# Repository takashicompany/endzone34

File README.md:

# EndZone34

ミニマルな34キーのキーボードです。  
LEDとOLED、MXソケットに対応しています。

# 組み立て方

## ビルドログ

- [いとうひよこさんのNote](https://note.com/tsubuan_145/n/n91b1f3b4b958)

## 1. 部品の確認

### キットに同梱されているもの

|項目|個数|備考|
|:--|:--|:--|
|PCB|1|
|トッププレート|1|
|ボトムプレート|1|
|側面プレート|2|左右有り。キースイッチをMXソケットで取り付ける場合は不要|
|ProMicroプレート|1|
|ProMicro側面プレート|2|
|M2ネジ 10mm|18|
|M2ナット|18|
|ダイオード|34|
|リセットスイッチ|1|
|ゴム足シール|8|

### ご自身で用意されるもの
|項目|個数|備考|
|:--|:--|:--|
|キースイッチ|34|Cherry MX互換|
|キーキャップ|34|
|Pro Micro|1|必要な場合はコンスルーもご用意ください|

### MXソケットを利用する際に必要な部品

PCBがMXソケットに対応しているため、スペーサーとネジを別途ご用意頂き、キースイッチの付け替えが可能になります。
(MXソケットを使用する場合は側面プレートを取り付けることはできません。)

|項目|個数|備考|
|:--|:--|:--|
|MXソケット|34||
|両雌ネジスペーサー 7mm|8|
|M2ネジ 4mm|16|

## 2. ダイオードのはんだ付け

### ① PCBの裏表の確認

**こちらが表面**  

**こちらは裏面**  

はんだ付けは**裏面**に行います

### ① マスキングテープで表面にはんだが漏れないようにする

(テープを見えやすくするために黒色のPCBで説明します)  

当キットではトッププレートとPCBを密着させる方式なので、表面にはんだが漏れて凹凸ができないように、マスキングテープなどで穴を塞ぎましょう。

### ② ダイオードをはんだづけする

https://user-images.githubusercontent.com/4215759/126895350-43ae4cd4-408b-4ff4-ab5c-2903e0420978.mov

PCBのダイオードのはんだづけ箇所の片方にはんだを乗せておき(予備はんだ)、ピンセットでダイオードを持ちながら予備はんだを溶かしながらダイオードをはんだづけします。  
片方のはんだづけが終わったら、動画と同じく反対側をはんだづけしましょう。

全部で34箇所あります。

## 3-a. キースイッチのはんだ付け

キースイッチをはんだ付けする場合は、以下の手順になります。

### ① トッププレートを取り出す

アクリル製のトッププレートを取り出します。  

ネジ穴部分にアクリル栓が詰まっている場合は、ピンセットやネジで押し出すと取り出すことができます。  
全てのネジ穴が空いていることを確認しましょう。  

トッププレートの台紙を剥がします。   
剥がしづらい場合は、台紙を少し濡らすと剥がれやすくなります。

下記の画像のように両面を剥がします。  

### ② トッププレートを仮止め

当キーボードキットは、PCBとトッププレートを密着させる必要があるため、キースイッチのはんだ付けの際にトッププレートがぐらつかないようにすると作業が楽になります。  
同梱しているネジとナットを使って、PCBの表側にトッププレートを固定しましょう。

あくまで仮止めですので、全ての箇所を固定しなくても問題ありません。
下記の画像は目安です。  
固定できたらPCBとトッププレートに隙間が無いことを確認してください。

### ③ キースイッチをはんだ付けする
PCBとトッププレートを固定できたら、キースイッチのはんだ付けを行います。  
キースイッチがズレないように、マスキングテープなどで固定すると作業が楽になります。

各キースイッチ、2箇所をはんだ付けします。  
**取付箇所毎にキースイッチの向きが異なります。**  

34個のキースイッチをはんだ付けできたら、高さがズレているものがないかを確認します。  
加えて、再びPCBとトッププレートの間に隙間が無いことを確認します。

## 3-b. MXソケットでキースイッチを取り付ける場合

キースイッチをMXソケットではんだ付けする際は、以下の方法になります。
なお、この場合は側面プレートではなく、スペーサーでトッププレートとボトムプレートを固定することとなります。

### ① PCBにMXソケットをはんだ付けする

### ② トッププレートを取り出す

「3-a. ① トッププレートを取り出す」と同様にトッププレートを取りだします。

### ③ トッププレートにキースイッチを取り付ける

PCBとトッププレートの仮止めとして、キースイッチを数個取り付けます。

以下は一例になります。  

キースイッチをいくつか取り付けた後に、PCBにはんだ付けしたMXソケットにトッププレートに仮止めしたキースイッチを取り付けます。

トッププレートがたわまないように気をつけながら、全てのMXソケットにキースイッチを付けていきます。

### ④ トッププレートにスペーサーを取り付ける

以下の赤丸の箇所にスペーサーを取り付けます。  
トッププレートとスペーサーをネジで固定します。  

下記の写真のように、トッププレートからネジで固定されたスペーサーがPCBを貫通してPCBの裏側に出ていると正しく取り付けられています。

## 4. リセットスイッチのはんだ付け
※リセットスイッチのはんだ付けは必須ではありません。組み立て後も、ピンセット等を用いて底面からリセット操作が可能です。

### ① PCBの裏面からリセットスイッチを差し込む

### ② PCBの表面からはんだづけをする

### ③ はんだ付けした部分を可能な限り平らにする

Pro Microとぶつかってしまう可能性があるので、ニッパーなどで平らにします。

### ④ 絶縁テープなどではんだ付け部分を覆う

## 5. Pro Microの取り付け

Pro Microをご用意いただきます。  
PCBはコンスルーとはんだ付けの両対応をしています。  

Pro Microのチップなどが載っていない方を表側にし、PCBの表側に指します。

一度ここで、ProMicroをPCなどに繋ぎ、ファームウェアを焼いて動作確認をすると問題があった際に、対処が容易です。  

ファームウェアは[こちら](https://github.com/takashicompany/endzone34/blob/master/README.md#%E3%83%95%E3%82%A1%E3%83%BC%E3%83%A0%E3%82%A6%E3%82%A7%E3%82%A2)。

## 6. Pro Microプレートの取り付け
まずはPro Microの側面プレートを取り付けます。  
側面プレートは二種類あるので、お好みで選んでください。  

台紙を剥がして、側面プレートを2枚トッププレートに載せます。    

次にPro Microプレートを取り付けます。  

台紙を剥がして、側面プレートの上に載せます。  

ネジとナットで固定します。  

裏面は下記の写真のようにナットで抑えます。  

MXソケットを利用する場合は、ナットの代わりにスペーサーを用いると良いです。

## 6. LEDの取り付け

LEDの取り付けは必須ではありません。一度組み立てた後で取り付けることでも可能です。  
LEDはWS2812Bを使用します。下記の画像の順番で取り付けます。 

取り付ける際に、PCBのプリント(角の塗りつぶし)とLEDの角の向きが合うようにします。 

まずは予備ハンダをします。利き腕側で手前の側の部分からはんだ付けをすると楽にできます。

一つのLEDの4箇所をはんだづけします。  

一つはんだ付けができたら、LEDが光るかを確認しましょう。  
USBでPCにキーボードを接続した後、`RGB_TOG`キーを押して、LEDが光るかを確認します。  

全部で9つのLEDを取り付けられることができます。  

## 7. ケースの組み立て

※ MXソケットでキースイッチを固定する場合は、側面プレートを取り付けることができません。

側面プレートを取りだします。側面プレートは左右で分かれています。

ボトムプレートも取りだします。  

台紙を取り外して、側面プレートとボトムプレートをネジとナットで取り付けます。

側面プレートとボトムプレートを取り付けた後は、ゴム足をケースに貼ります。

### MXソケットでキースイッチを取り付けた場合

以下の赤丸の箇所をネジ止めします。  

# 8. ファームウェア

## [QMK Firmware](https://github.com/qmk/qmk_firmware)
- QMK Firmware公式に[マージ済み](https://github.com/qmk/qmk_firmware/pull/13847)です
- [keyboards/takashicompany/endzone34](https://github.com/qmk/qmk_firmware/tree/master/keyboards/takashicompany/endzone34)にファームウェアを用意しております。

## VIA用のファームウェアは[こちら](https://github.com/takashicompany/endzone34/releases/download/via-0.0.3/takashicompany_endzone34_via.hex)
- [Remap](https://remap-keys.app/)へ登録済みですので、上記のVIA対応したファームウェアをPro Microに書き込むことでブラウザからキーマップの変更が可能です。
- (2021/09/01) OLEDの表示とレイヤー数を8にしたファームウェアを追加しました。

# 9. OLEDが点灯しない場合
ファームウェアの容量の関係でVIAのファームウェアにOLEDが入っていないことがあります。  
疎通を確認するために、[デフォルトのファームウェア](https://github.com/takashicompany/endzone34/releases/download/via-0.0.2/takashicompany_endzone34_default.hex)で一度OLEDの確認をお願いします。

# 10. 自慢する

完成しましたら、ぜひSNSなどに写真を投稿頂ければと思います。  
Twitterのハッシュタグは`#EndZone34`を付けていただけば幸いです。  
キットを組み立てた感想や、キーボードを使った所感などをお待ちしております！  

また、毎週日曜日の１9時より実施されている[#KEEP_PD](https://twitter.com/hashtag/KEEB_PD?f=live)に投稿頂くこともオススメです。  
開催の告知は[@KEEB_PD](https://twitter.com/KEEB_PD)にて行われております。

ご不明な点などございましたら、[@takashicompany](https://twitter.com/takashicompany)にメンションやDM頂ければと思います！

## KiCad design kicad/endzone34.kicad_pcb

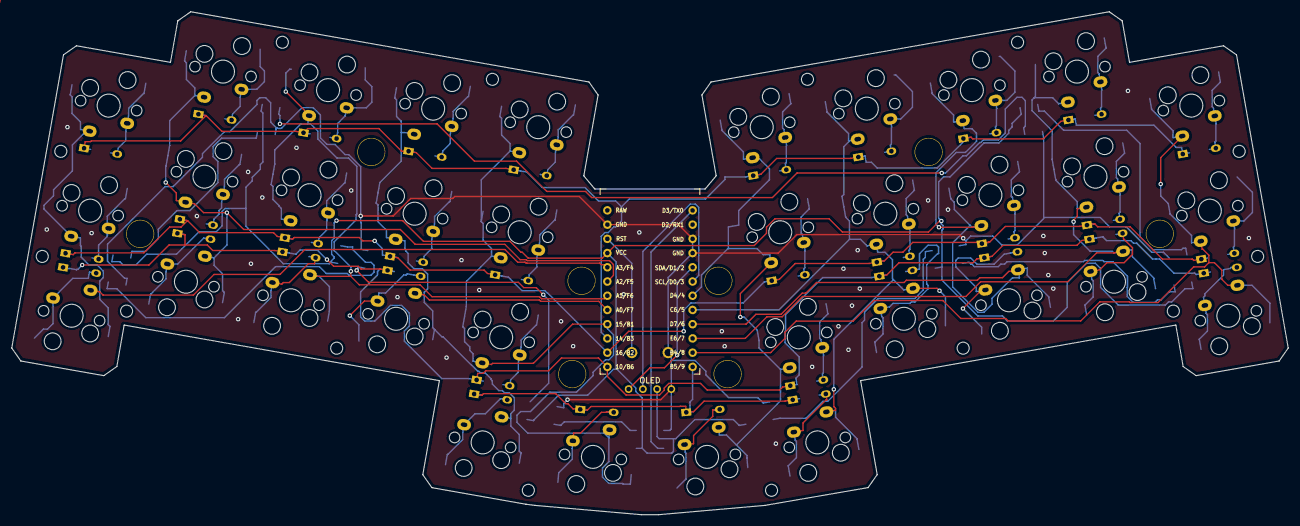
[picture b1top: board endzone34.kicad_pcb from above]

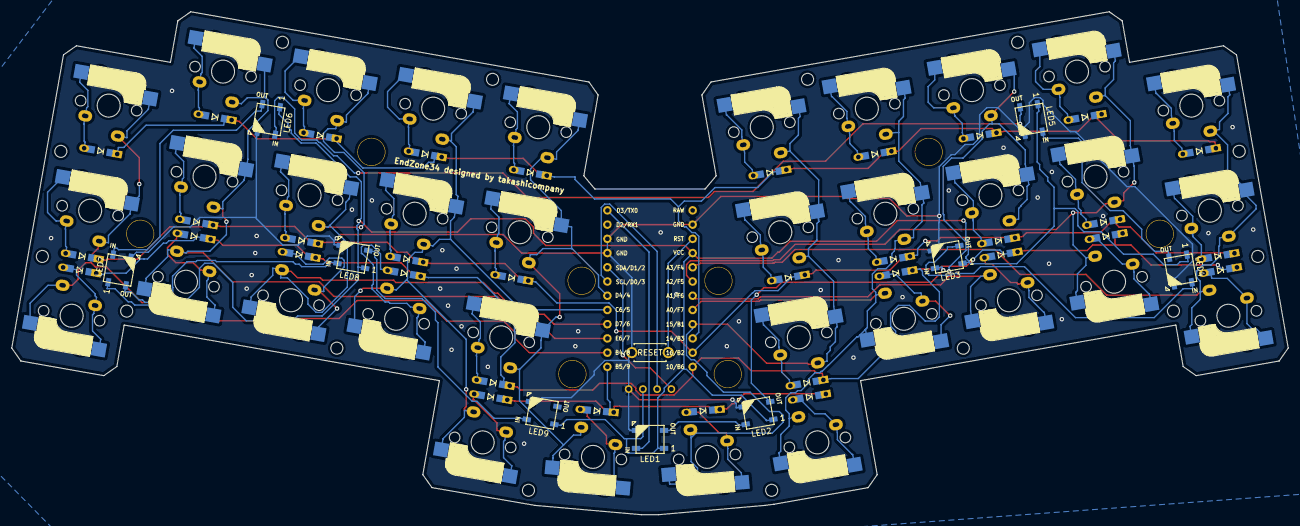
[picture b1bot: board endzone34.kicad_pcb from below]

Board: 2 copper layers, 227.9 x 89.8 mm, 102 parts (44 on the bottom side), 62 nets.

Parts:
D1, D2, D3, D4, D5, D6, D7, D8, D9, D10, D11, D12, D13, D14, D15, D16, D17, D18, D19, D20, D21, D22, D23, D24, D25, D26, D27, D28, D29, D30, D31, D32, D33, D34: DIODE; D3_TH_SMD_v2
LED1, LED2, LED3, LED4, LED5, LED6, LED7, LED8, LED9: WS2812B
OL1: OLED; OLED_v2
RESET_SW1: SW_Push; ResetSW_1side
Ref01, Ref02, Ref03, Ref04, Ref05, Ref06, Ref007, Ref08: Val**; HOLE
Ref11, Ref12, Ref13, Ref14, Ref15, Ref16, Ref17, Ref18, Ref19, Ref20, Ref21, Ref22, Ref23, Ref24: M2_Hole
SW1, SW2, SW3, SW4, SW5, SW6, SW7, SW8, SW9, SW10, SW11, SW12, SW13, SW14, SW15, SW16, SW17, SW18, SW19, SW20, SW21, SW22, SW23, SW24, SW25, SW26, SW27, SW28, SW29, SW30, SW31, SW32, SW33, SW34: SW_Push; CherryMX_TH-Hotswap
U1: ProMicro_r; ProMicro_v3.5_print-inside

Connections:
GND: LED1.3, LED2.3, LED3.3, LED4.3, LED5.3, LED6.3, LED7.3, LED8.3, LED9.3, OL1.4, RESET_SW1.2, U1.3, U1.4, U1.23
unnamed: D1.2, SW1.2
unnamed: D2.2, SW2.2
unnamed: D3.2, SW3.2
unnamed: D4.2, SW4.2
unnamed: D5.2, SW5.2
unnamed: D6.2, SW6.2
unnamed: D7.2, SW7.2
unnamed: D8.2, SW8.2
unnamed: D9.2, SW9.2
unnamed: D10.2, SW10.2
unnamed: D11.2, SW11.2
unnamed: D12.2, SW12.2
unnamed: D13.2, SW13.2
unnamed: D14.2, SW14.2
unnamed: D15.2, SW15.2
unnamed: D16.2, SW16.2
unnamed: D17.2, SW17.2
unnamed: D18.2, SW18.2
unnamed: D19.2, SW19.2
unnamed: D20.2, SW20.2
unnamed: D21.2, SW21.2
unnamed: D22.2, SW22.2
unnamed: D23.2, SW23.2
unnamed: D24.2, SW24.2
unnamed: D25.2, SW25.2
unnamed: D26.2, SW26.2
unnamed: D27.2, SW27.2
unnamed: D28.2, SW28.2
unnamed: D29.2, SW29.2
unnamed: D30.2, SW30.2
unnamed: D31.2, SW31.2
unnamed: D32.2, SW32.2
unnamed: D33.2, SW33.2
unnamed: D34.2, SW34.2
unnamed: LED1.2, LED2.4
unnamed: LED2.2, LED3.4
unnamed: LED3.2, LED4.4
unnamed: LED4.2, LED5.4
unnamed: LED5.2, LED6.4
unnamed: LED6.2, LED7.4
unnamed: LED7.2, LED8.4
unnamed: LED8.2, LED9.4
SCL: OL1.2, U1.6
SDA: OL1.1, U1.5
VCC: LED1.1, LED2.1, LED3.1, LED4.1, LED5.1, LED6.1, LED7.1, LED8.1, LED9.1, OL1.3, U1.21
col0: SW1.1, SW11.1, SW21.1, U1.20
col1: SW2.1, SW12.1, SW22.1, U1.19
col2: SW3.1, SW13.1, SW23.1, U1.18
col3: SW4.1, SW14.1, SW24.1, SW31.1, U1.17
col4: SW5.1, SW15.1, SW25.1, SW32.1, U1.16
col5: SW6.1, SW16.1, SW26.1, SW33.1, U1.7
col6: SW7.1, SW17.1, SW27.1, SW34.1, U1.8
col7: SW8.1, SW18.1, SW28.1, U1.9
col8: SW9.1, SW19.1, SW29.1, U1.10
col9: SW10.1, SW20.1, SW30.1, U1.11
led: LED1.4, U1.1
reset: RESET_SW1.1, U1.22
row0: D1.1, D2.1, D3.1, D4.1, D5.1, D6.1, D7.1, D8.1, D9.1, D10.1, U1.15
row1: D11.1, D12.1, D13.1, D14.1, D15.1, D16.1, D17.1, D18.1, D19.1, D20.1, U1.14
row2: D21.1, D22.1, D23.1, D24.1, D25.1, D26.1, D27.1, D28.1, D29.1, D30.1, U1.13
row3: D31.1, D32.1, D33.1, D34.1, U1.12

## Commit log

2021-07-25 概要を書いた
2021-07-25 画像や動画を入れた
2021-07-25 画像の表示方法をHTML型に
2021-07-31 途中まで書いた
2021-07-31 MXソケットに対しての記述
2021-08-01 とりあえず書いた。
2021-08-01 写真の改行を整理
2021-08-01 画像を追加
2021-08-01 画像のパスを変更
2021-08-02 画像を更新
2021-08-02 リネーム
2021-08-02 ガーバーファイルをアップロード
2021-08-06 ファームウェアに関して書いた
2021-08-06 VIAのファームウェアへのリンク
2021-08-06 ファームウェアへのジャンプ
2021-08-07 Remapのことを書いた
2021-08-13 QMK公式にマージされたので、その内容を記載
2021-08-22 説明書を修正
2021-08-26 MXソケットに関する記載を追加
2021-08-26 改行を修正
2021-08-30 OLEDの件を追加
2021-08-31 OLEDの項目を足しました
2021-09-18 写真を追加
2021-10-27 画像の追加”
2021-11-13 add image
2024-09-06 kicad
